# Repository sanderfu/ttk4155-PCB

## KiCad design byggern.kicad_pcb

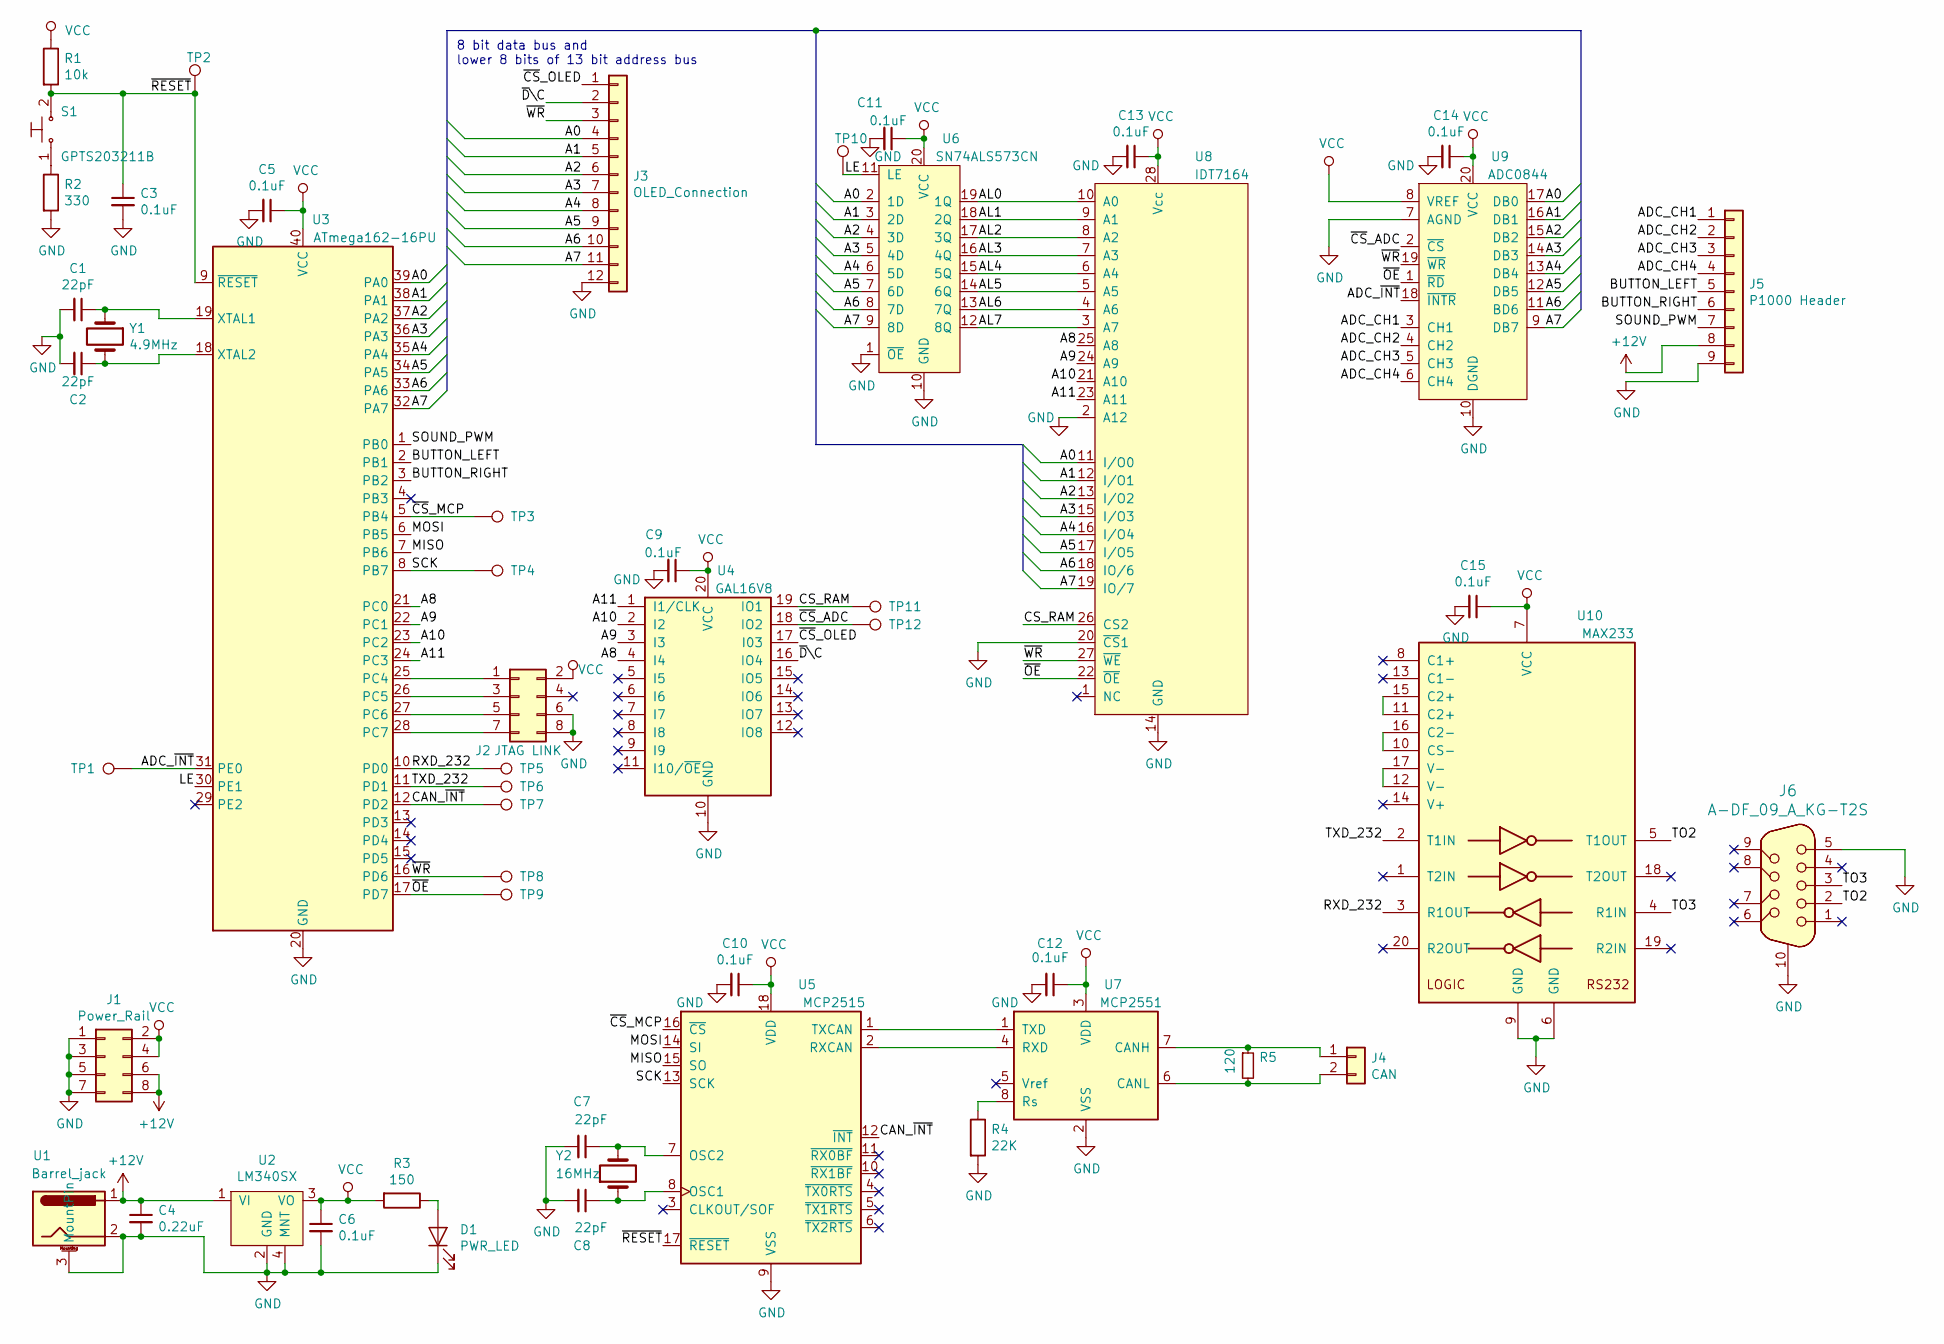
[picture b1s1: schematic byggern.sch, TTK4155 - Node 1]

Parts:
C1, C2, C7, C8: 22pF; C_0805_2012Metric_Pad1.15x1.40mm_HandSolder
C3, C5, C6, C9, C10, C11, C12, C13, C14, C15: 0.1uF; C_0805_2012Metric_Pad1.15x1.40mm_HandSolder
C4: 0.22uF; C_0805_2012Metric_Pad1.15x1.40mm_HandSolder
D1: PWR_LED; LED_0805_2012Metric_Pad1.15x1.40mm_HandSolder
J1: Power_Rail; PinHeader_2x04_P2.54mm_Vertical
J2: JTAG LINK; PinHeader_2x04_P2.54mm_Vertical
J3: OLED_Connection; PinHeader_1x12_P2.54mm_Vertical
J4: CAN; PinHeader_1x02_P2.54mm_Vertical
J5: P1000 Header; PinHeader_1x09_P2.54mm_Vertical
J6: A-DF_09_A_KG-T2S; DSUB-9_Receptical_A-DF_09_A_KG-T2S; MPN A-DF 09 A/KG-T2S; Digi-Key_PN AE10921-ND
R1: 10k; R_0805_2012Metric_Pad1.15x1.40mm_HandSolder
R2: 330; R_0805_2012Metric_Pad1.15x1.40mm_HandSolder
R3: 150; R_0805_2012Metric_Pad1.15x1.40mm_HandSolder
R4: 22K; R_0805_2012Metric_Pad1.15x1.40mm_HandSolder
R5: 120; R_0805_2012Metric_Pad1.15x1.40mm_HandSolder
S1: GPTS203211B; PushButton_12x12mm_THT_GPTS203211B; MPN GPTS203211B; Digi-Key_PN CW181-ND
TP1, TP2, TP3, TP4, TP5, TP6, TP7, TP8, TP9, TP10, TP11, TP12: TestPoint; TestPoint_Pad_D1.5mm
U1: Barrel_jack; BarrelJack_Horizontal
U2: LM340SX
U3: ATmega162-16PU; DIP-40_W15.24mm_Socket
U4: GAL16V8; DIP-20_W7.62mm_Socket
U5: MCP2515; DIP-18_W7.62mm_Socket
U6: SN74ALS573CN; DIP-20_W7.62mm_Socket
U7: MCP2551; DIP-8_W7.62mm_Socket
U8: IDT7164; DIP-28_W7.62mm_Socket
U9: ADC0844; DIP-20_W7.62mm_Socket
U10: MAX233; DIP-20_W7.62mm_Socket
Y1: 4.9MHz; Crystal_SMD_HC49-SD_HandSoldering
Y2: 16MHz; Crystal_SMD_HC49-SD_HandSoldering

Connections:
+12V: C4.1, J1.6, J1.8, J5.8, U1.1, U2.1 (VI)
/A0: J3.4, U3.39 (PA0), U6.2 (1D), U8.11 (I/O0), U9.17 (DB0)
/A1: J3.5, U3.38 (PA1), U6.3 (2D), U8.12 (I/O1), U9.16 (DB1)
/A2: J3.6, U3.37 (PA2), U6.4 (3D), U8.13 (I/O2), U9.15 (DB2)
/A3: J3.7, U3.36 (PA3), U6.5 (4D), U8.15 (I/O3), U9.14 (DB3)
/A4: J3.8, U3.35 (PA4), U6.6 (5D), U8.16 (I/O4), U9.13 (DB4)
/A5: J3.9, U3.34 (PA5), U6.7 (6D), U8.17 (I/O5), U9.12 (DB5)
/A6: J3.10, U3.33 (PA6), U6.8 (7D), U8.18 (IO/6), U9.11 (BD6)
/A7: J3.11, U3.32 (PA7), U6.9 (8D), U8.19 (IO/7), U9.9 (DB7)
/A8: U3.21 (PC0), U4.4 (I4), U8.25 (A8)
/A9: U3.22 (PC1), U4.3 (I3), U8.24 (A9)
/A10: U3.23 (PC2), U4.2 (I2), U8.21 (A10)
/A11: U3.24 (PC3), U4.1 (I1/CLK), U8.23 (A11)
/ADC_CH1: J5.1, U9.3 (CH1)
/ADC_CH2: J5.2, U9.4 (CH2)
/ADC_CH3: J5.3, U9.5 (CH3)
/ADC_CH4: J5.4, U9.6 (CH4)
/ADC_~INT~: TP1.1, U3.31 (PE0), U9.18 (~INTR)
/AL0: U6.19 (1Q), U8.10 (A0)
/AL1: U6.18 (2Q), U8.9 (A1)
/AL2: U6.17 (3Q), U8.8 (A2)
/AL3: U6.16 (4Q), U8.7 (A3)
/AL4: U6.15 (5Q), U8.6 (A4)
/AL5: U6.14 (6Q), U8.5 (A5)
/AL6: U6.13 (7Q), U8.4 (A6)
/AL7: U6.12 (8Q), U8.3 (A7)
/BUTTON_LEFT: J5.5, U3.2 (PB1)
/BUTTON_RIGHT: J5.6, U3.3 (PB2)
/CAN_~INT~: TP7.1, U3.12 (PD2), U5.12 (~INT)
/CS_RAM: TP11.1, U4.19 (IO1), U8.26 (CS2)
/LE: TP10.1, U3.30 (PE1), U6.11 (LE)
/MISO: U3.7 (PB6), U5.15 (SO)
/MOSI: U3.6 (PB5), U5.14 (SI)
/RXD_232: TP5.1, U3.10 (PD0), U10.3 (R1OUT)
/SCK: TP4.1, U3.8 (PB7), U5.13 (SCK)
/SOUND_PWM: J5.7, U3.1 (PB0)
/TO2: J6.2, U10.5 (T1OUT)
/TO3: J6.3, U10.4 (R1IN)
/TXD_232: TP6.1, U3.11 (PD1), U10.2 (T1IN)
/~CS~_ADC: TP12.1, U4.18 (IO2), U9.2 (~CS~)
/~CS~_MCP: TP3.1, U3.5 (PB4), U5.16 (~CS)
/~CS~_OLED: J3.1, U4.17 (I03)
/~D~\C: J3.2, U4.16 (IO4)
/~OE~: TP9.1, U3.17 (PD7), U8.22 (~OE), U9.1 (~RD)
/~RESET~: C3.1, R1.2, S1.2, TP2.1, U3.9 (~RESET), U5.17 (~RESET)
/~WR~: J3.3, TP8.1, U3.16 (PD6), U8.27 (~WE), U9.19 (~WR)
GND: C1.2, C2.2, C3.2, C4.2, C5.2, C6.2, C7.2, C8.2, C9.2, C10.2, C11.2, C12.2, C13.2, C14.2, C15.2, D1.1 (K), J1.1, J1.3, J1.5, J1.7, J2.6, J2.8, J3.12, J5.9, J6.5, J6.10, R2.2, R4.2, U1.2, U1.3 (MountPin), U2.2 (GND), U2.4 (MNT), U3.20 (GND), U4.10 (GND), U5.9 (VSS), U6.1 (~OE), U6.10 (GND), U7.2 (VSS), U8.2 (A12), U8.14 (GND), U8.20 (~CS~1), U9.7 (AGND), U9.10 (DGND), U10.6 (GND), U10.9 (GND)
unnamed: C1.1, U3.19 (XTAL1), Y1.1
unnamed: C2.1, U3.18 (XTAL2), Y1.2
unnamed: C7.1, U5.7 (OSC2), Y2.2
unnamed: C8.1, U5.8 (OSC1), Y2.1
unnamed: D1.2 (A), R3.1
unnamed: J2.1, U3.25 (PC4)
unnamed: J2.3, U3.26 (PC5)
unnamed: J2.5, U3.27 (PC6)
unnamed: J2.7, U3.28 (PC7)
unnamed: J4.1, R5.1, U7.7 (CANH)
unnamed: J4.2, R5.2, U7.6 (CANL)
unnamed: R2.1, S1.1
unnamed: R4.1, U7.8 (Rs)
unnamed: U5.1 (TXCAN), U7.1 (TXD)
unnamed: U5.2 (RXCAN), U7.4 (RXD)
unnamed: U10.10 (CS-), U10.16 (C2-)
unnamed: U10.11 (C2+), U10.15 (C2+)
unnamed: U10.12 (V-), U10.17 (V-)
VCC: C5.1, C6.1, C9.1, C10.1, C11.1, C12.1, C13.1, C14.1, C15.1, J1.2, J1.4, J2.2, R1.1, R3.2, U2.3 (VO), U3.40 (VCC), U4.20 (VCC), U5.18 (VDD), U6.20 (VCC), U7.3 (VDD), U8.28 (Vcc), U9.8 (VREF), U9.20 (VCC), U10.7 (VCC)

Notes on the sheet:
8 bit data bus and lower 8 bits of 13 bit address bus

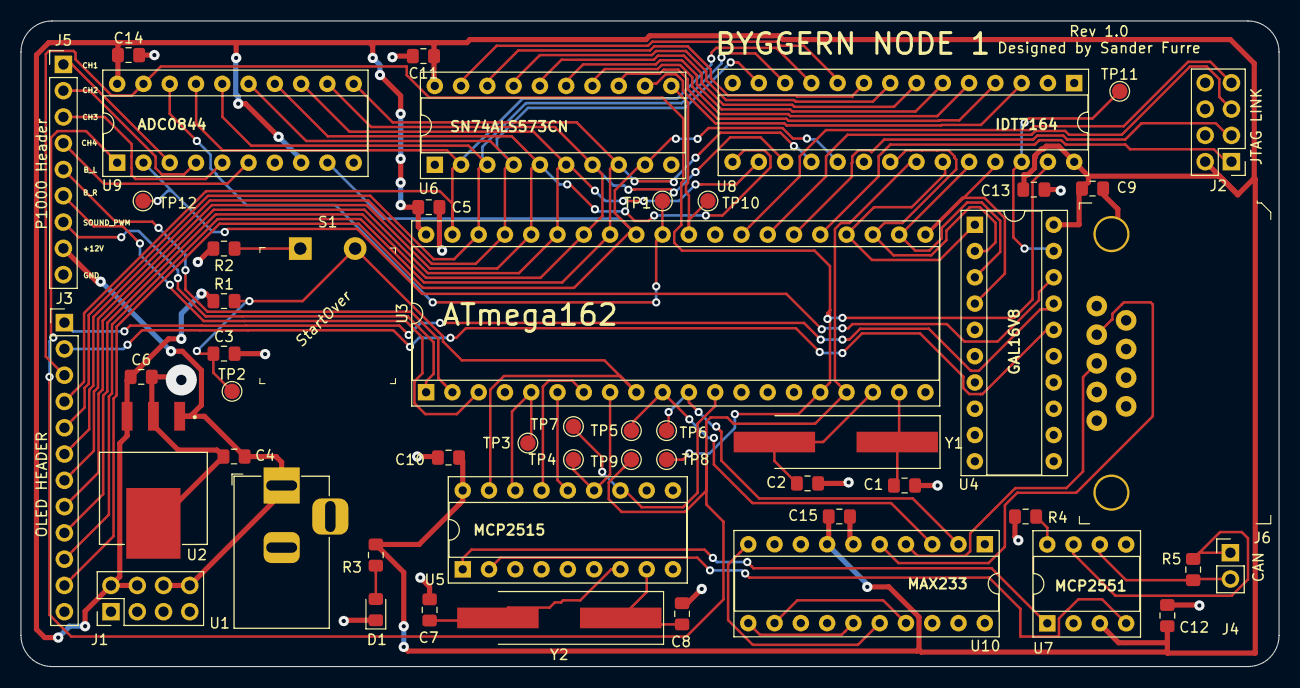
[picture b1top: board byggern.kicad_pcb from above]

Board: 2 copper layers, 121.6 x 62.4 mm, 52 parts (0 on the bottom side), 66 nets.

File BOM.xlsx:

Component | Amount | Designators | DigiKey Ref |  | I handleliste
22pF 0805 Capacitor | 4 | C1, C2, C7, C8 | 399-1113-1-ND‎ |  | j
0.1 uF 0805 Capacitor | 10 | C3, C5, C6, C9, C10, C11, C12, C13, C14, C15 | 1276-1007-1-ND |  | j
0.22uF 0805 Capacitor | 1 | C4 | 1276-6478-1-ND |  | j
PWR_LED 0805 | 3 | D1 | 732-4982-1-ND |  | j
Power_rail header 8 pin (2x4) | 1 | J1 | 732-5296-ND |  | j
JTAG LINK header 8 pin (2x4) | 1 | J2 | 732-5296-ND |  | j
OLED_Connection header 12 pin | 1 | J3 | 732-5323-ND |  | j
CAN header 2 pin | 1 | J4 | 732-5315-ND |  | j
P1000 header 9 pin | 1 | J5 | 732-5322-ND |  | j
DB9 Connector (UART) | 1 | J6 | AE10921-ND |  | j
10k 0805 Resistor | 1 | R1 | RNCP0805FTD10K0CT-ND‎ |  | j
330 0805 resistor | 1 | R2 | A106061CT-ND‎ |  | j
150 0805 resistor | 1 | R3 | RNCP0805FTD150RCT-ND |  | j
22k 0805 resistor | 1 | R4 | RR12P22.0KDCT-ND‎ |  | j
120 0805 resistor | 1 | R5 | A129738CT-ND |  | j
Pushbutton | 2 | S1 | GPTS203211B |  | j
Barrel jack | 2 | U1 | CP-002A-ND |  | j
LM340SX | 2 | U2 | LM340SX-5.0/NOPBCT-ND |  | j
DIP-40_W15.24 (For MCU) | 1 | U3 | ‎ED3048-5-ND‎ |  | j
DIP-20_W7.62 (For GAL) | 1 | U4 | ‎ED3054-5-ND‎ |  | j
DIP-18_W7.62(for MCP2515) | 1 | U5 | ED3047-5-ND‎ |  | j
DIP-20_W7.62 (for SN74ALS…) | 1 | U6 | ‎ED3054-5-ND‎ |  | j
DIP-8_W7.62 (for mcp 2551) | 1 | U7 | AE9986-ND‎ |  | j
DIP-28_W7.62 (for IDT7164) | 1 | U8 | ED3050-5-ND‎ |  | j
DIP-20_W7.62 (for ADC0844) | 1 | U9 | ‎ED3054-5-ND‎ |  | j
DIP-20_W7.62 (for MAX233) | 1 | U10 | ‎ED3054-5-ND‎ |  | j
Crystal SMD_HC49-SD 4.9152 Hz | 2 | Y1 | 631-1007-1-ND |  | j
Crystal SMD_HC49-SD 16 MHz | 2 | Y2 | 631-1017-1-ND |  | j
Cable to OLED | 2 |  | 1568-1938-ND |  | j
Cable to P1000 | 1 |  | 1568-1513-ND |  | j

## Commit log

2019-10-09 Update schematic with usart interface
2019-10-09 Complete schematic, quality check remaining
2019-10-09 Correct warnings from electrical error check and change tri-state to output rule to ignore, no critical warnings left
2019-10-09 Minor cleanup and add .gitignore
2019-10-09 Correct error in gitignore and add power to P1000-header
2019-10-09 Change name of P1000 Header
2019-10-10 Start assignment of footprints
2019-10-11 Create footprint library with ICs specific to the project
2019-10-11 Add footprints to components
2019-10-11 Start routing PCB
2019-10-12 Change footprints of ICs to DIPs and Close to finish routing
2019-10-15 Add BOM (Last commit was unsuccesful at it)
2019-10-15 Add fabrication files
2019-10-15 Fix errors and update BOM
2019-10-23 Add schematic and PCB render
